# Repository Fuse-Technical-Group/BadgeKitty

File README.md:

# Fuse Badgekitty

A fun handout for conferences and tradeshows designed by the Fuse CATS group in Lititz PA

If you have any questions about the CATS group feel free to reach out cats@fuse-tg.com

If you're curious about what fuse does check us out at https://fuse-tg.com

## Authors

- [@andybabin](https://www.github.com/octokatherine)
- [@mkohler99](https://www.github.com/mkohler99)
- [@Fuse-Technical-Group](https://github.com/Fuse-Technical-Group)

## Features

- 2 super attractive neopixel eyes
- A tiny buzzer to annoy all your friends
- A whopping 4096kB of flash storage space
- Dual power source options, USB-C or CR2023 battery
- Hidden programs to unlock by being social in meatspace (just ask the authors how!)
- Ability to reprogram via a UPDI programmer

## Usage/Examples

### Normal Operation

Insert a CR2032 battery into the holder or plug into a usb-c power supply capable of supplying 5volts. Patterns will start automatically and the device will goto sleep after 10 minutes.

### Highpower Mode
Hold in the headpat button while powering on. This will increase the LED brightness and disable the sleep functionality.

## Lessons Learned

- 4096kB of flash is a tiny amount
- CR2032 batteries are terrible

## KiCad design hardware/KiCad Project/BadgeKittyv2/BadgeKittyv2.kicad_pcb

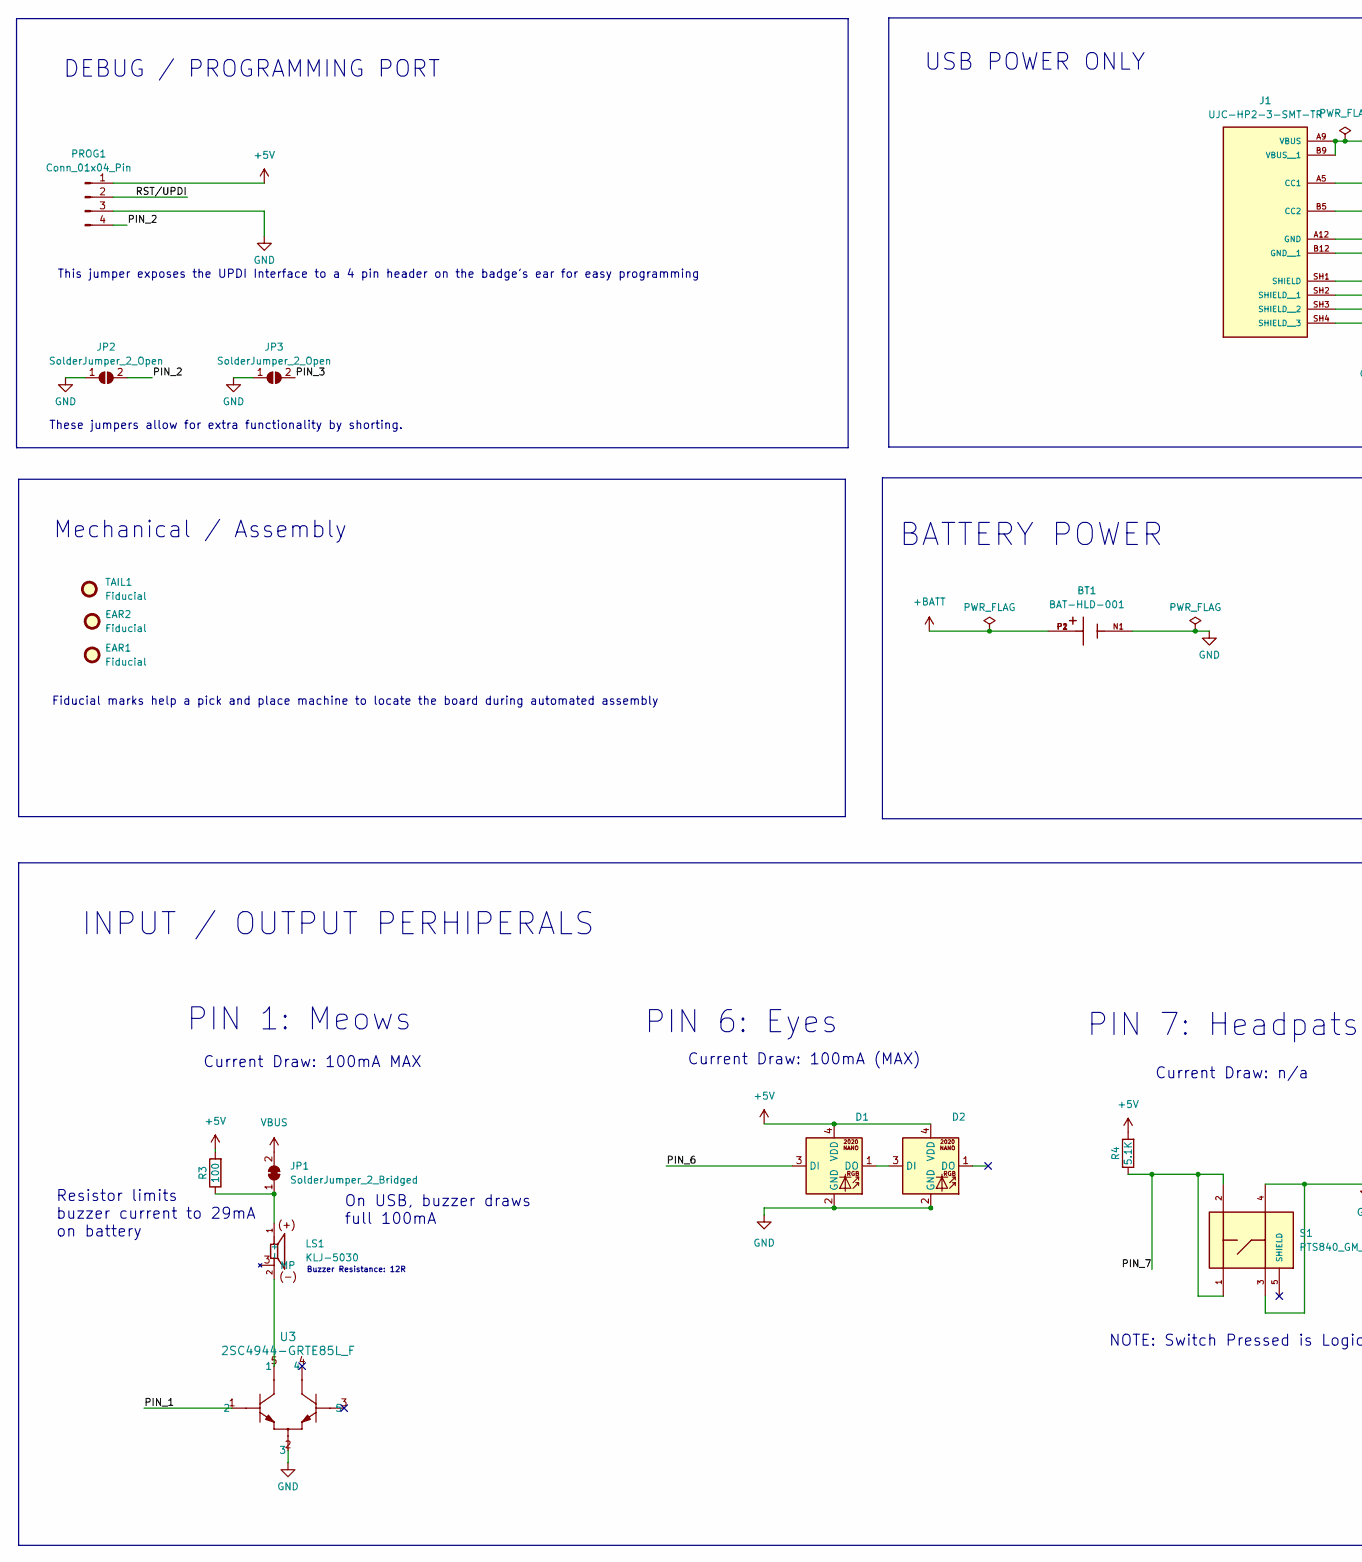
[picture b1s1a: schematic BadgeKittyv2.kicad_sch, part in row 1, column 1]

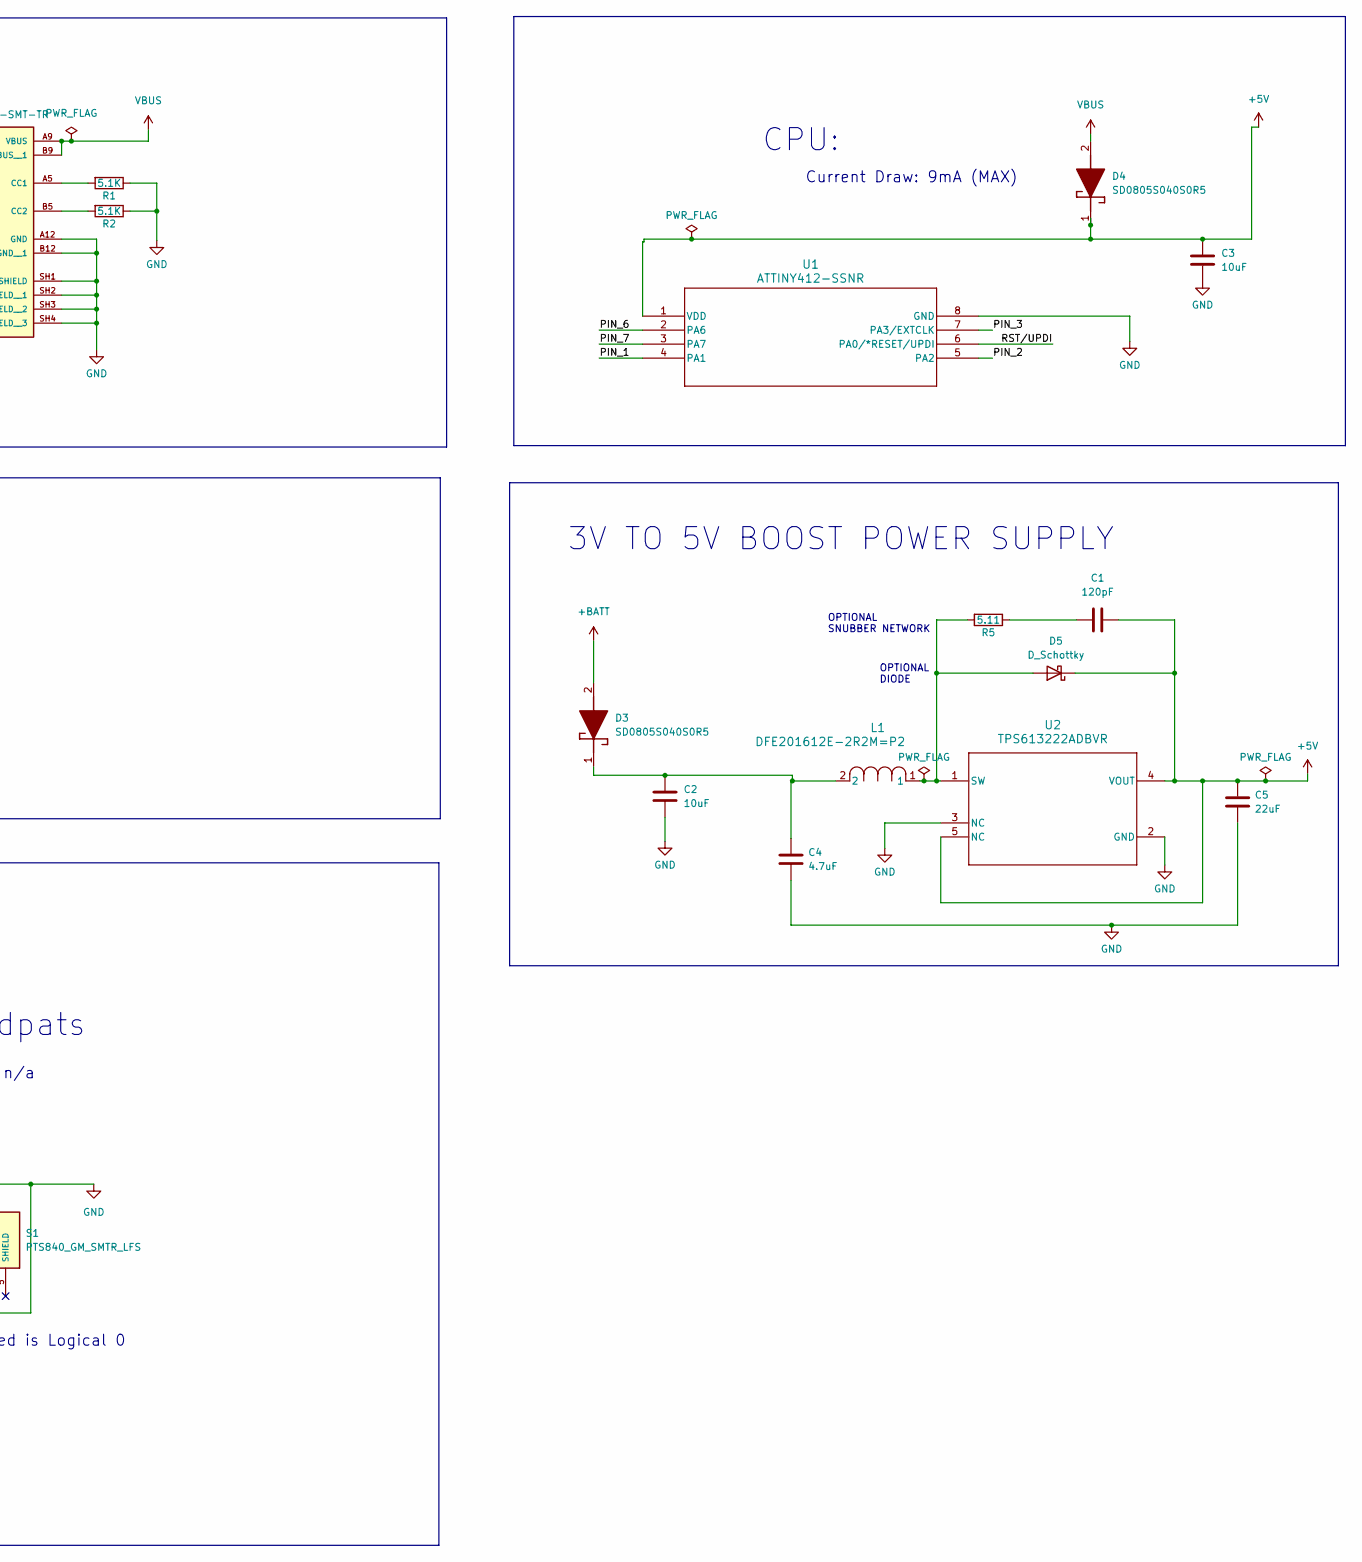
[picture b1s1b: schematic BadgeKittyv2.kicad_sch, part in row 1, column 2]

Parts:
BT1: BAT-HLD-001; BAT_BAT-HLD-001; PARTREV C
C1: 120pF; C_0805_2012Metric
C2, C3: 10uF; C_0805_2012Metric
C4: 4.7uF; C_0805_2012Metric
C5: 22uF; C_0805_2012Metric
D1, D2: LED_WS2812B-2020_PLCC4_2.0x2.0mm
D3, D4: SD0805S040S0R5; SD0805; Mouser Part Number 581-SD0805S040S0R5
D5: D_Schottky; ZLLS400TA_DIO
EAR1, EAR2: Fiducial; Fiducial_1mm_Mask2mm
J1: UJC-HP2-3-SMT-TR; CUI_UJC-HP2-3-SMT-TR; PARTREV 1.01
JP1: SolderJumper_2_Bridged; SolderJumper-2_P1.3mm_Bridged_Pad1.0x1.5mm
JP2, JP3: SolderJumper_2_Open; SolderJumper-2_P1.3mm_Open_TrianglePad1.0x1.5mm
L1: DFE201612E-2R2M=P2; IND_DFE2016_MUR
LS1: KLJ-5030; PARTREV 1.01
PROG1: Conn_01x04_Pin; PinHeader_1x04_P2.54mm_Vertical_Stealth
R1, R2, R4: 5.1K; R_0805_2012Metric
R3: 100; R_0805_2012Metric
R5: 5.11; R_0805_2012Metric
S1: PTS840_GM_SMTR_LFS; SW_PTS840GMSMTRLFS
TAIL1: Fiducial; Fiducial_1mm_Mask2mm
U1: ATTINY412-SSNR; SOIC8_SA_SST_MCH
U2: TPS613222ADBVR; DBV0005A_N
U3: 2SC4944-GRTE85L_F; SOT-353 USV_TOS

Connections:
+5V: C1.2, C3.1, C5.1, D1.4 (VDD), D2.4 (VDD), D4.1 (K), D5.1 (K), PROG1.1, R3.2, R4.2, U1.1 (VDD), U2.4 (VOUT), U2.5 (NC)
+BATT: BT1.P1, BT1.P2, D3.2 (A)
/PIN_1: U1.4 (PA1), U3.1 (2)
/PIN_2: JP2.2 (B), PROG1.4, U1.5 (PA2)
/PIN_3: JP3.2 (B), U1.7 (PA3/EXTCLK)
/PIN_6: D1.3 (DI), U1.2 (PA6)
/PIN_7: R4.1, S1.1, S1.2, U1.3 (PA7)
/RST/UPDI: PROG1.2, U1.6 (PA0/*RESET/UPDI)
GND: BT1.N1, C2.2, C3.2, C4.2, C5.2, D1.2 (GND), D2.2 (GND), J1.A12 (GND), J1.B12 (GND__1), J1.SH1 (SHIELD), J1.SH2 (SHIELD__1), J1.SH3 (SHIELD__2), J1.SH4 (SHIELD__3), JP2.1 (A), JP3.1 (A), PROG1.3, R1.1, R2.1, S1.3, S1.4, U1.8 (GND), U2.2 (GND), U2.3 (NC), U3.2 (3)
unnamed: C1.1, R5.1
unnamed: D1.1 (DO), D2.3 (DI)
unnamed: C2.1, C4.1, D3.1 (K), L1.2
unnamed: J1.A5 (CC1), R1.2
unnamed: J1.B5 (CC2), R2.2
unnamed: JP1.1 (A), LS1.1 (+), R3.1
unnamed: LS1.2 (-), U3.5 (1)
unnamed: D5.2 (A), L1.1, R5.2, U2.1 (SW)
VBUS: D4.2 (A), J1.A9 (VBUS), J1.B9 (VBUS__1), JP1.2 (B)

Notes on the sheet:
These jumpers allow for extra functionality by shorting.
Current Draw: 100mA MAX
BATTERY POWER
Current Draw: 9mA (MAX)
Current Draw: 100mA (MAX)
USB POWER ONLY
OPTIONAL DIODE
PIN 7: Headpats
PIN 6: Eyes
OPTIONAL SNUBBER NETWORK
NOTE: Switch Pressed is Logical 0
PIN 1: Meows
Resistor limits buzzer current to 29mA on battery
3V TO 5V BOOST POWER SUPPLY
Fiducial marks help a pick and place machine to locate the board during automated assembly
INPUT / OUTPUT PERHIPERALS
Current Draw: n/a
On USB, buzzer draws full 100mA
This jumper exposes the UPDI Interface to a 4 pin header on the badge's ear for easy programming
Buzzer Resistance: 12R
CPU:
Mechanical / Assembly
DEBUG / PROGRAMMING PORT

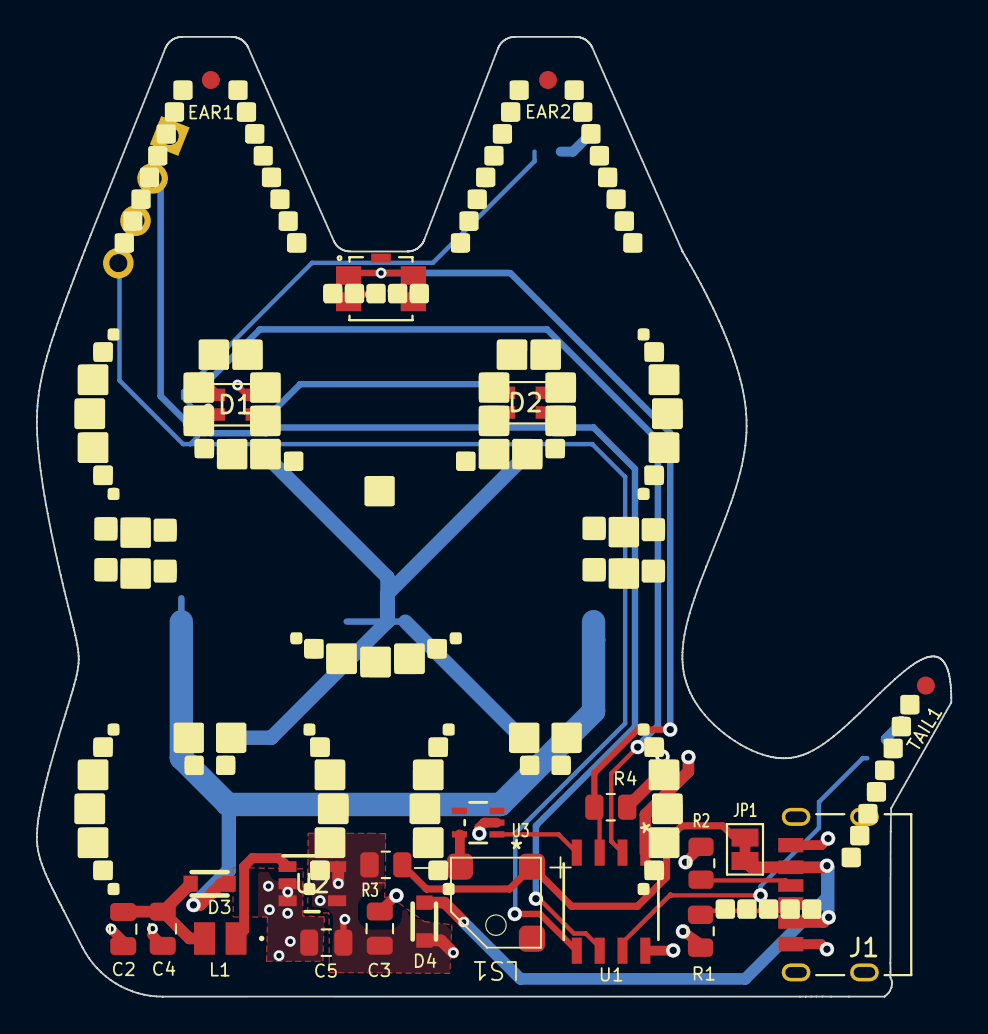
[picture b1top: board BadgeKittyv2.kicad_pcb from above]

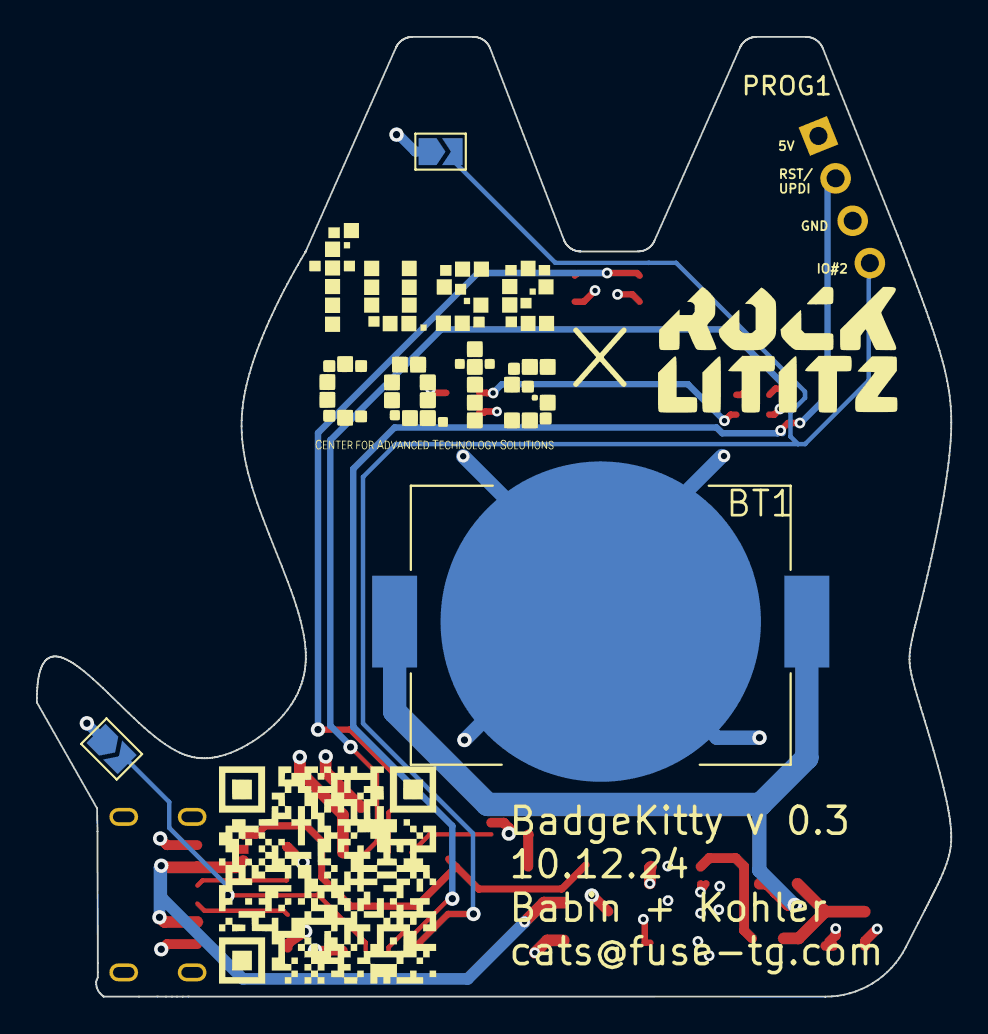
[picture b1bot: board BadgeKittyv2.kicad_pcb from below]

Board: 4 copper layers, 50.8 x 53.3 mm, 27 parts (3 on the bottom side), 17 nets.

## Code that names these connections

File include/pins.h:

#define EYES 0 //PA6
//#define PATS 7
#define PATS PIN_PA7
#define MEOWS 2 //PA1
#define EAR_GPI PIN_PA2
#define TAIL_GPI PIN_PA3

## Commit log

2024-11-06 added hardware folder
2024-11-06 Updated hardware documentation to latest
2024-11-06 First major push?
2024-11-06 First code upload
2024-11-06 updatd timeout
2024-11-06 highpower mode
2024-11-06 updated the highpower cheatcode
2024-11-07 code cleanup
2024-11-07 Minjor updates
2024-11-07 fixed rainbow bug...there is something about rainbows
2024-11-07 added email to readme
2024-11-07 added a blue look to finish out the flash size
2024-12-06 we broke everything
2024-12-07 removing noise and code cleanup
